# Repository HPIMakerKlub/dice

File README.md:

# dice
A simple dice pcb to be used a student events.

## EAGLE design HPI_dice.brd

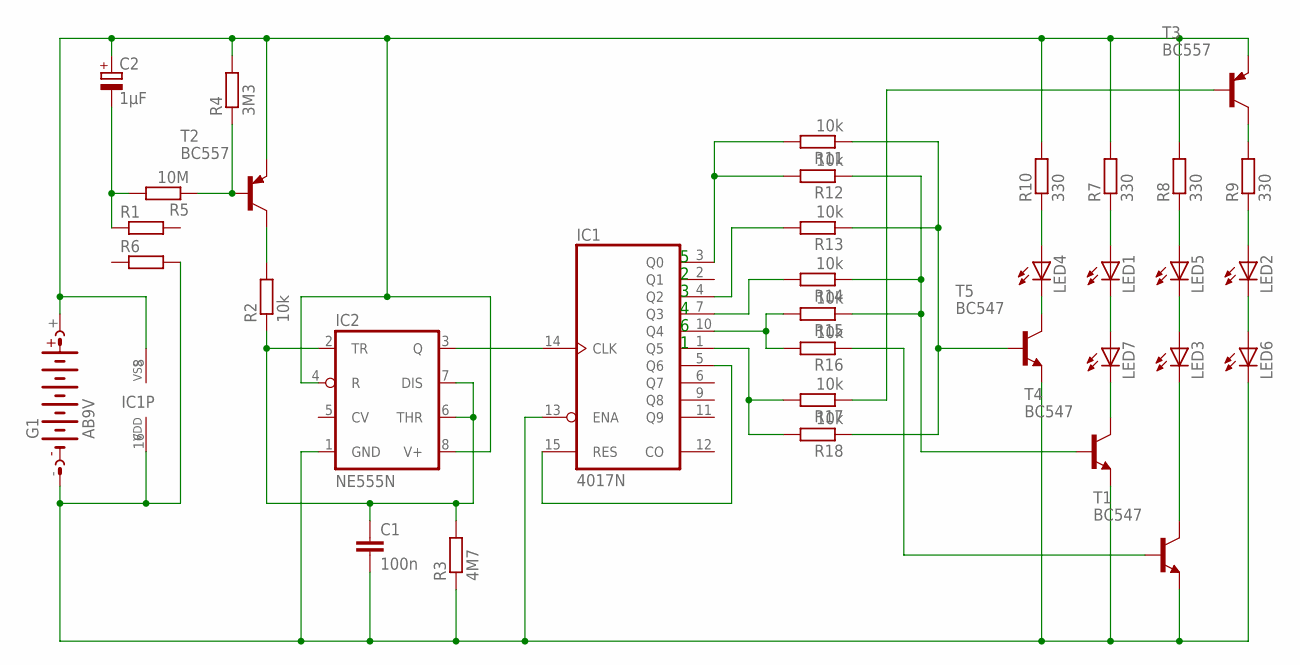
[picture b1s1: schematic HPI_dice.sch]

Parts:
C1: 100n; C050-025X075
C2: 1µF; E2,5-6
G1: AB9V
IC1: 4017N; DIL16
IC2: NE555N; DIL08
LED1, LED2, LED3, LED4, LED5, LED6, LED7: LED3MM
R1, R6: R-EU_0207/10; 0207/10
R2, R11, R12, R13, R14, R15, R16, R17, R18: 10k; 0207/10
R3: 4M7; 0207/10
R4: 3M3; 0207/10
R5: 10M; 0207/10
R7, R8, R9, R10: 330; 0207/10
T1, T4, T5: BC547; TO92
T2, T3: BC557; TO92

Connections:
+9V: C2.+, G1.+, IC1.8 (VSS), IC2.4 (R), IC2.8 (V+), R4.2, R7.2, R8.2, R10.2, T2.1 (E), T3.1 (E)
GND: C1.2, G1.-, IC1.13 (ENA), IC1.16 (VDD), IC2.1 (GND), LED6.K (C), R3.1, R6.2, T1.1 (E), T4.1 (E), T5.1 (E)
unnamed: IC1.5 (Q6), IC1.15 (RES)
unnamed: R2.2, T2.3 (C)
unnamed: IC1.14 (CLK), IC2.3 (Q)
unnamed: C1.1, IC2.2 (TR), IC2.6 (THR), IC2.7 (DIS), R2.1, R3.2
unnamed: R4.1, R5.1, T2.2 (B)
unnamed: C2.-, R1.1, R5.2
unnamed: LED1.K (C), LED7.A
unnamed: LED3.A, LED5.K (C)
unnamed: LED2.K (C), LED6.A
unnamed: R9.2, T3.3 (C)
unnamed: LED2.A, R9.1
unnamed: LED5.A, R8.1
unnamed: LED1.A, R7.1
unnamed: LED3.K (C), T1.3 (C)
unnamed: LED7.K (C), T4.3 (C)
unnamed: LED4.A, R10.1
unnamed: LED4.K (C), T5.3 (C)
unnamed: IC1.3 (Q0), R11.2, R12.2
unnamed: R11.1, R13.1, R18.1, T5.2 (B)
unnamed: R12.1, R14.1, R15.1, T4.2 (B)
unnamed: IC1.4 (Q2), R13.2
unnamed: IC1.7 (Q3), R14.2
unnamed: IC1.10 (Q4), R15.2, R16.2
unnamed: R16.1, T1.2 (B)
unnamed: IC1.1 (Q5), R17.2, R18.2
unnamed: R17.1, T3.2 (B)

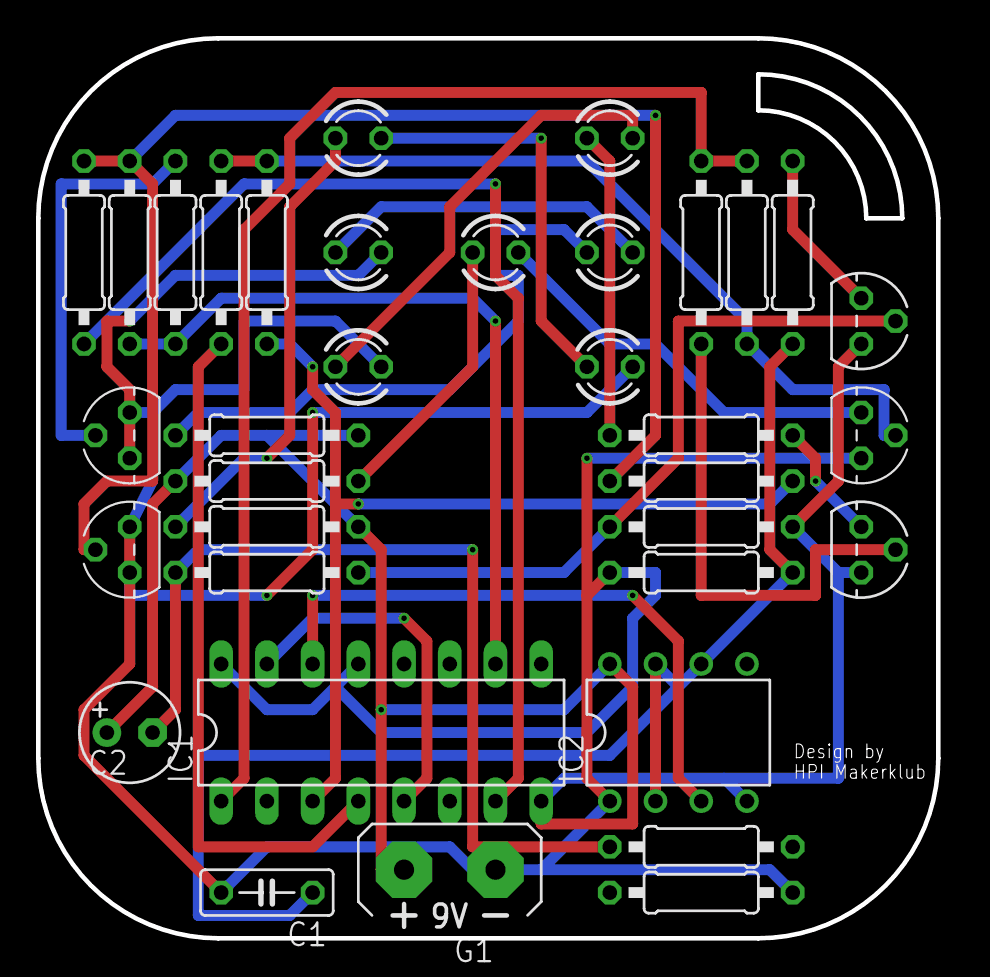
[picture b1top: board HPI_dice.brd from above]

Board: 2 copper layers, 50.8 x 50.0 mm, 35 parts (0 on the bottom side), 28 nets.

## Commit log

2016-07-08 Added schematic
2016-07-08 Added boardlayout
2016-07-08 Board layout improvement
